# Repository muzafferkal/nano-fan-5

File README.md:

An adruino nano v3 shield schematic & pcb with two fan and a power connector.
fans are controlled by pwm pins.

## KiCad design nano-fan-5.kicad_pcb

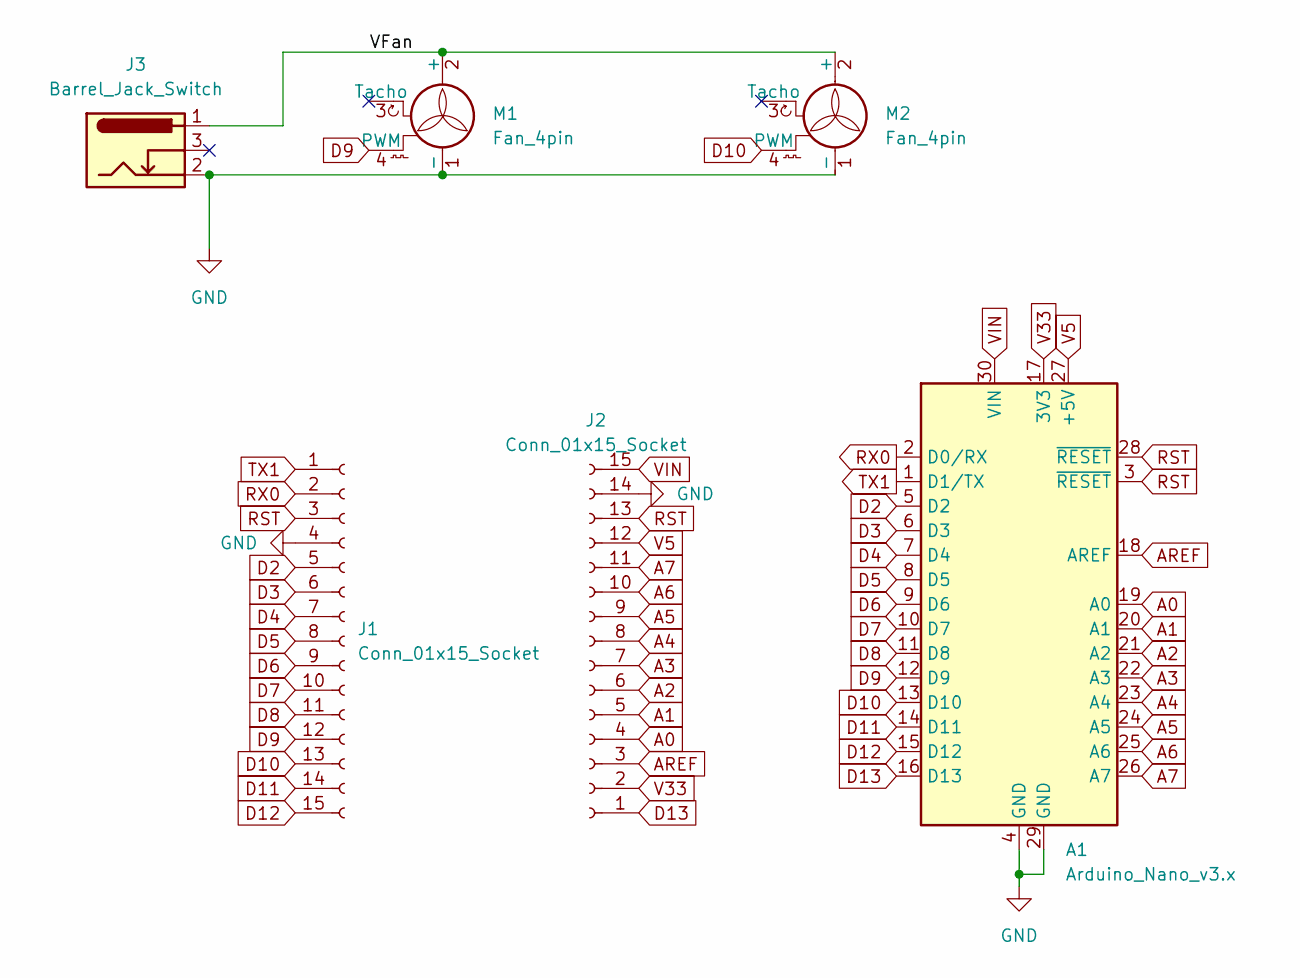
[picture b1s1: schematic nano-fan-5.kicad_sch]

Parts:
A1: Arduino_Nano_v3.x; Arduino_Nano
J1, J2: Conn_01x15_Socket; PinSocket_1x15_P2.54mm_Vertical
J3: Barrel_Jack_Switch; BarrelJack_CUI_PJ-079BH_Horizontal
M1, M2: Fan_4pin; Molex_KK-254_AE-6410-04A_1x04_P2.54mm_Vertical

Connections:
/VFan: J3.1, M1.2 (+), M2.2 (+)
A0: A1.19 (A0), J2.4
A1: A1.20 (A1), J2.5
A2: A1.21 (A2), J2.6
A3: A1.22 (A3), J2.7
A4: A1.23 (A4), J2.8
A5: A1.24 (A5), J2.9
A6: A1.25 (A6), J2.10
A7: A1.26 (A7), J2.11
AREF: A1.18 (AREF), J2.3
D2: A1.5 (D2), J1.5
D3: A1.6 (D3), J1.6
D4: A1.7 (D4), J1.7
D5: A1.8 (D5), J1.8
D6: A1.9 (D6), J1.9
D7: A1.10 (D7), J1.10
D8: A1.11 (D8), J1.11
D9: A1.12 (D9), J1.12, M1.4 (PWM)
D10: A1.13 (D10), J1.13, M2.4 (PWM)
D11: A1.14 (D11), J1.14
D12: A1.15 (D12), J1.15
D13: A1.16 (D13), J2.1
GND: A1.4 (GND), A1.29 (GND), J1.4, J2.14, J3.2, M1.1 (-), M2.1 (-)
RST: A1.3 (~RESET), A1.28 (~RESET), J1.3, J2.13
RX0: A1.2 (D0/RX), J1.2
TX1: A1.1 (D1/TX), J1.1
V5: A1.27 (+5V), J2.12
V33: A1.17 (3V3), J2.2
VIN: A1.30 (VIN), J2.15

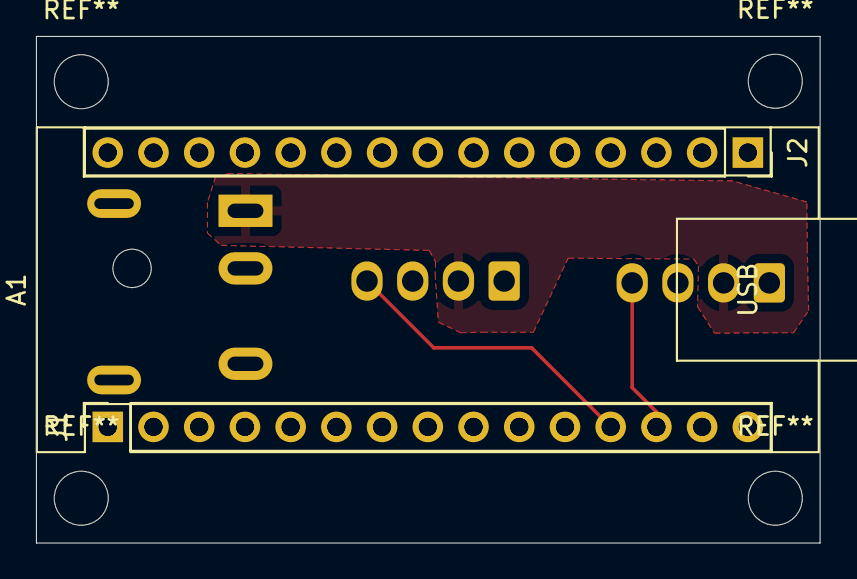
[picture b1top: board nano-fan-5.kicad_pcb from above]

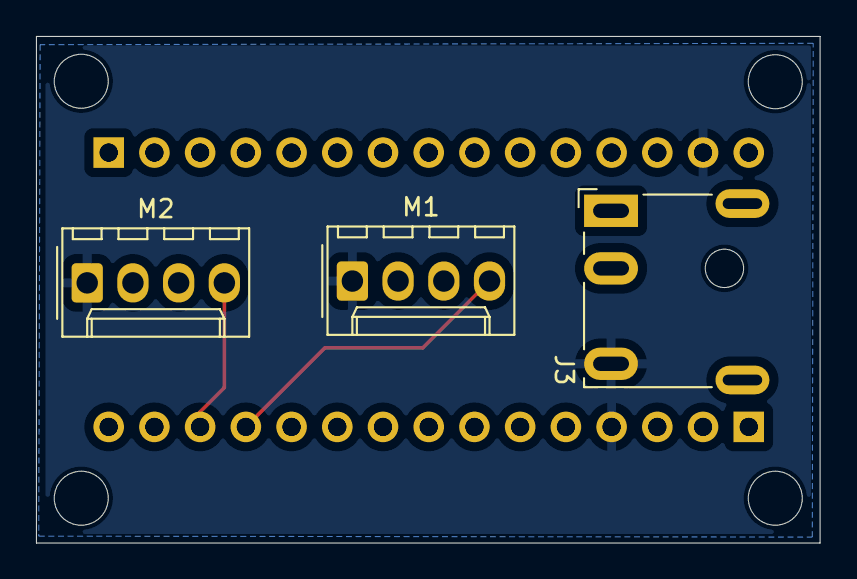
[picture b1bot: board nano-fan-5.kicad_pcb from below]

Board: 2 copper layers, 43.5 x 28.1 mm, 6 parts (3 on the bottom side), 29 nets.

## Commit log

2025-01-27 initial add
2025-01-27 update files and add bom csv
